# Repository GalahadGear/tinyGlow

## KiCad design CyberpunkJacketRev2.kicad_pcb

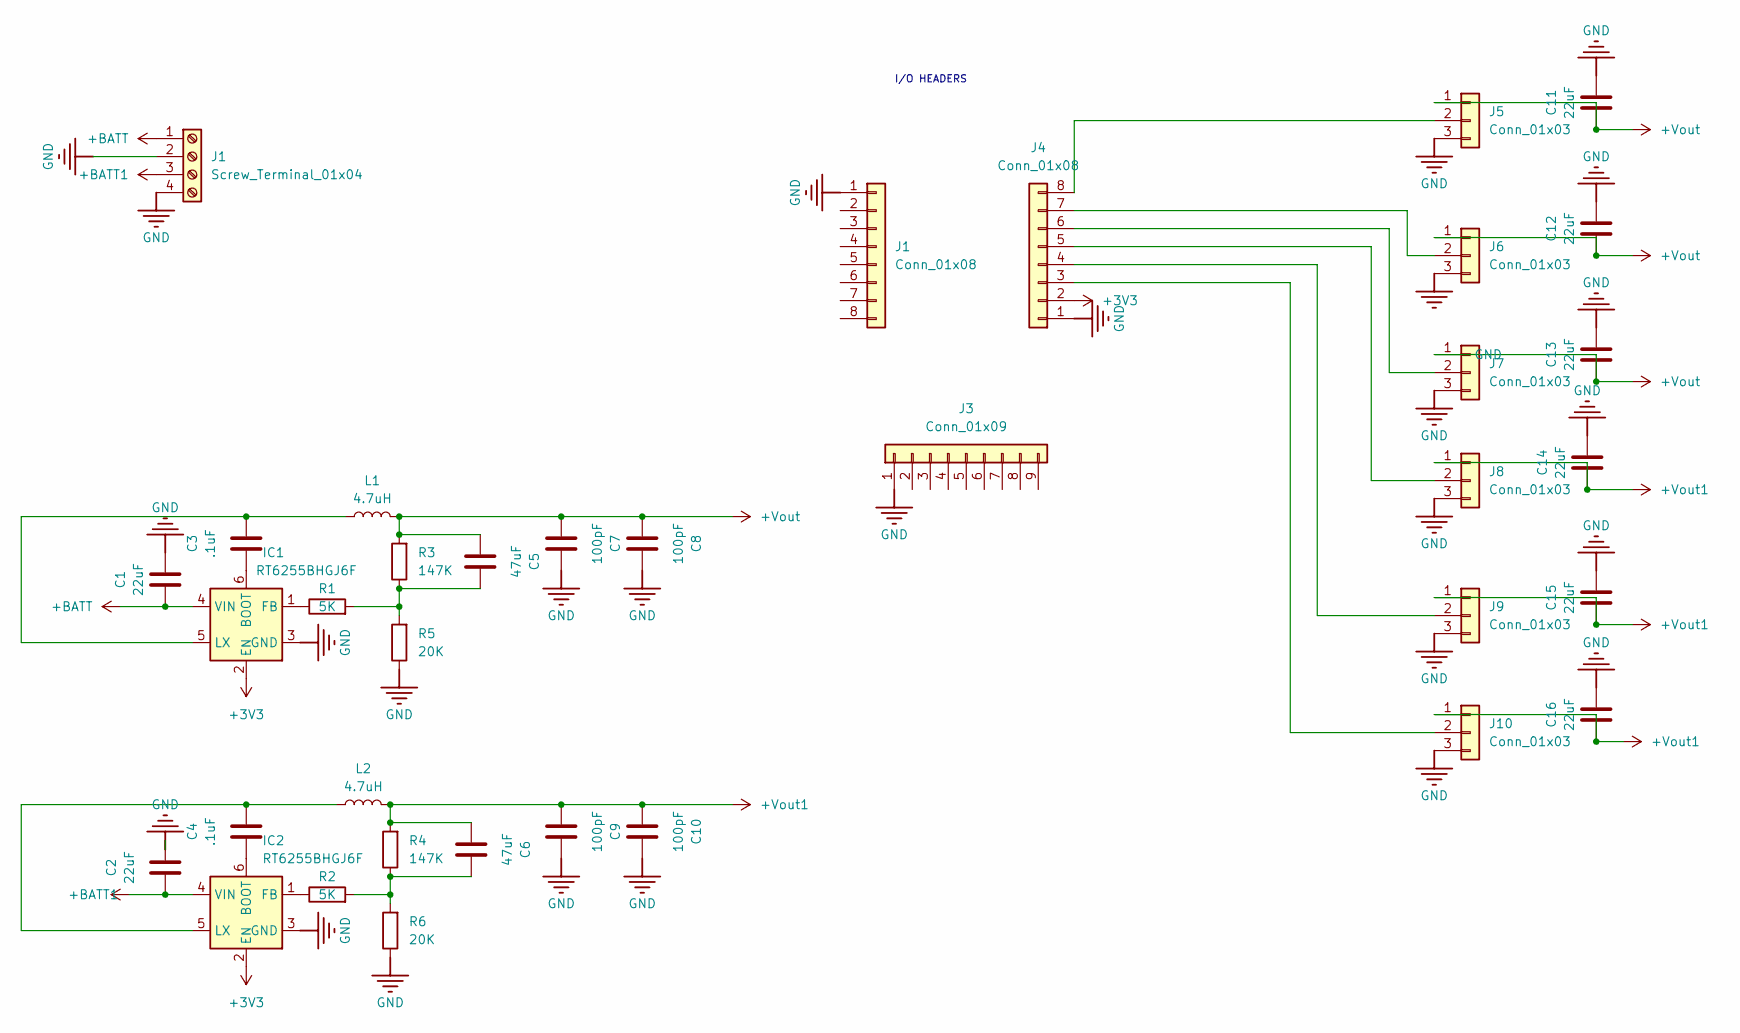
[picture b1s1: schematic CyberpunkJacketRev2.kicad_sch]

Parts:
C1, C2, C11, C12, C13, C14, C15, C16: 22uF; C_0603_1608Metric
C3, C4: .1uF; C_0603_1608Metric
C5, C6: 47uF; C_0603_1608Metric
C7, C8, C9, C10: 100pF; C_0603_1608Metric
IC1, IC2: RT6255BHGJ6F; TSOT-23-6_HandSoldering
J1: Screw_Terminal_01x04; FanPinHeader_1x04_P2.54mm_Vertical
J3: Conn_01x09; PinHeader_1x09_P2.54mm_Vertical
J4: Conn_01x08; PinHeader_1x08_P2.54mm_Vertical
J5, J6, J7, J8, J9, J10: Conn_01x03; PinHeader_1x03_P2.54mm_Vertical
L1, L2: 4.7uH; SPM6530T-4R7M
R1, R2: 5K; R_0603_1608Metric
R3, R4: 147K; R_0603_1608Metric
R5, R6: 20K; R_0603_1608Metric

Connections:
+3V3: IC1.2 (EN), IC2.2 (EN), J4.2
+BATT1: C2.1, IC2.4 (VIN), J1.3
+Vout: C5.1, C7.1, C8.1, C11.2, C12.2, C13.2, J5.1, J6.1, J7.1, L1.2, R3.2
+Vout1: C6.1, C9.1, C10.1, C14.2, C15.2, C16.2, J8.1, J9.1, J10.1, L2.2, R4.2
unnamed: C5.2, R1.2, R3.1, R5.2
unnamed: C6.2, R2.2, R4.1, R6.2
unnamed: C3.1, IC1.6 (BOOT)
unnamed: IC1.1 (FB), R1.1
unnamed: C3.2, IC1.5 (LX), L1.1
unnamed: C4.1, IC2.6 (BOOT)
unnamed: IC2.1 (FB), R2.1
unnamed: C4.2, IC2.5 (LX), L2.1
unnamed: J4.4, J9.2
unnamed: J4.5, J8.2
unnamed: J4.6, J7.2
unnamed: J4.7, J6.2
unnamed: J4.8, J5.2
unnamed: J4.3, J10.2

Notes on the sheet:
I/O HEADERS

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
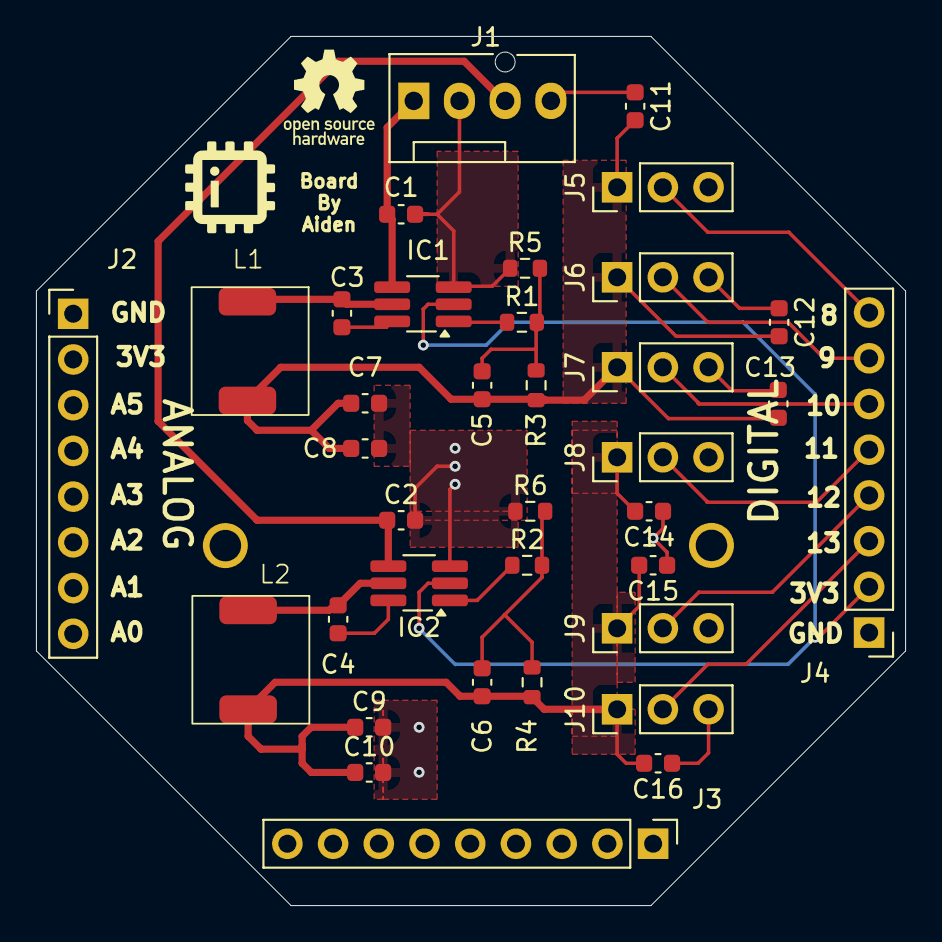
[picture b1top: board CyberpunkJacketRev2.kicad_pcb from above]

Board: 2 copper layers, 48.3 x 48.3 mm, 36 parts (0 on the bottom side), 20 nets.

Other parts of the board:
J2: Conn_01x08; PinHeader_1x08_P2.54mm_Vertical
